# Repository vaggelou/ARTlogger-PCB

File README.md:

# ARTlogger-PCB
This is the PCB design of the ARTlogger, a data logging device for the ART16 racecar.

This is the PCB design for the ARTlogger project, a project that was developed in order to produce a data-logger for racing purpose, during my time in Aristotle Racing Team (ART), the Formula Student team of Aristotle University of Thessaloniki, Greece.

This datalogger was used in the ART16, the 5th race car produced by the team.

The PCB was designed using KiCAD, an open source PCB design tool.

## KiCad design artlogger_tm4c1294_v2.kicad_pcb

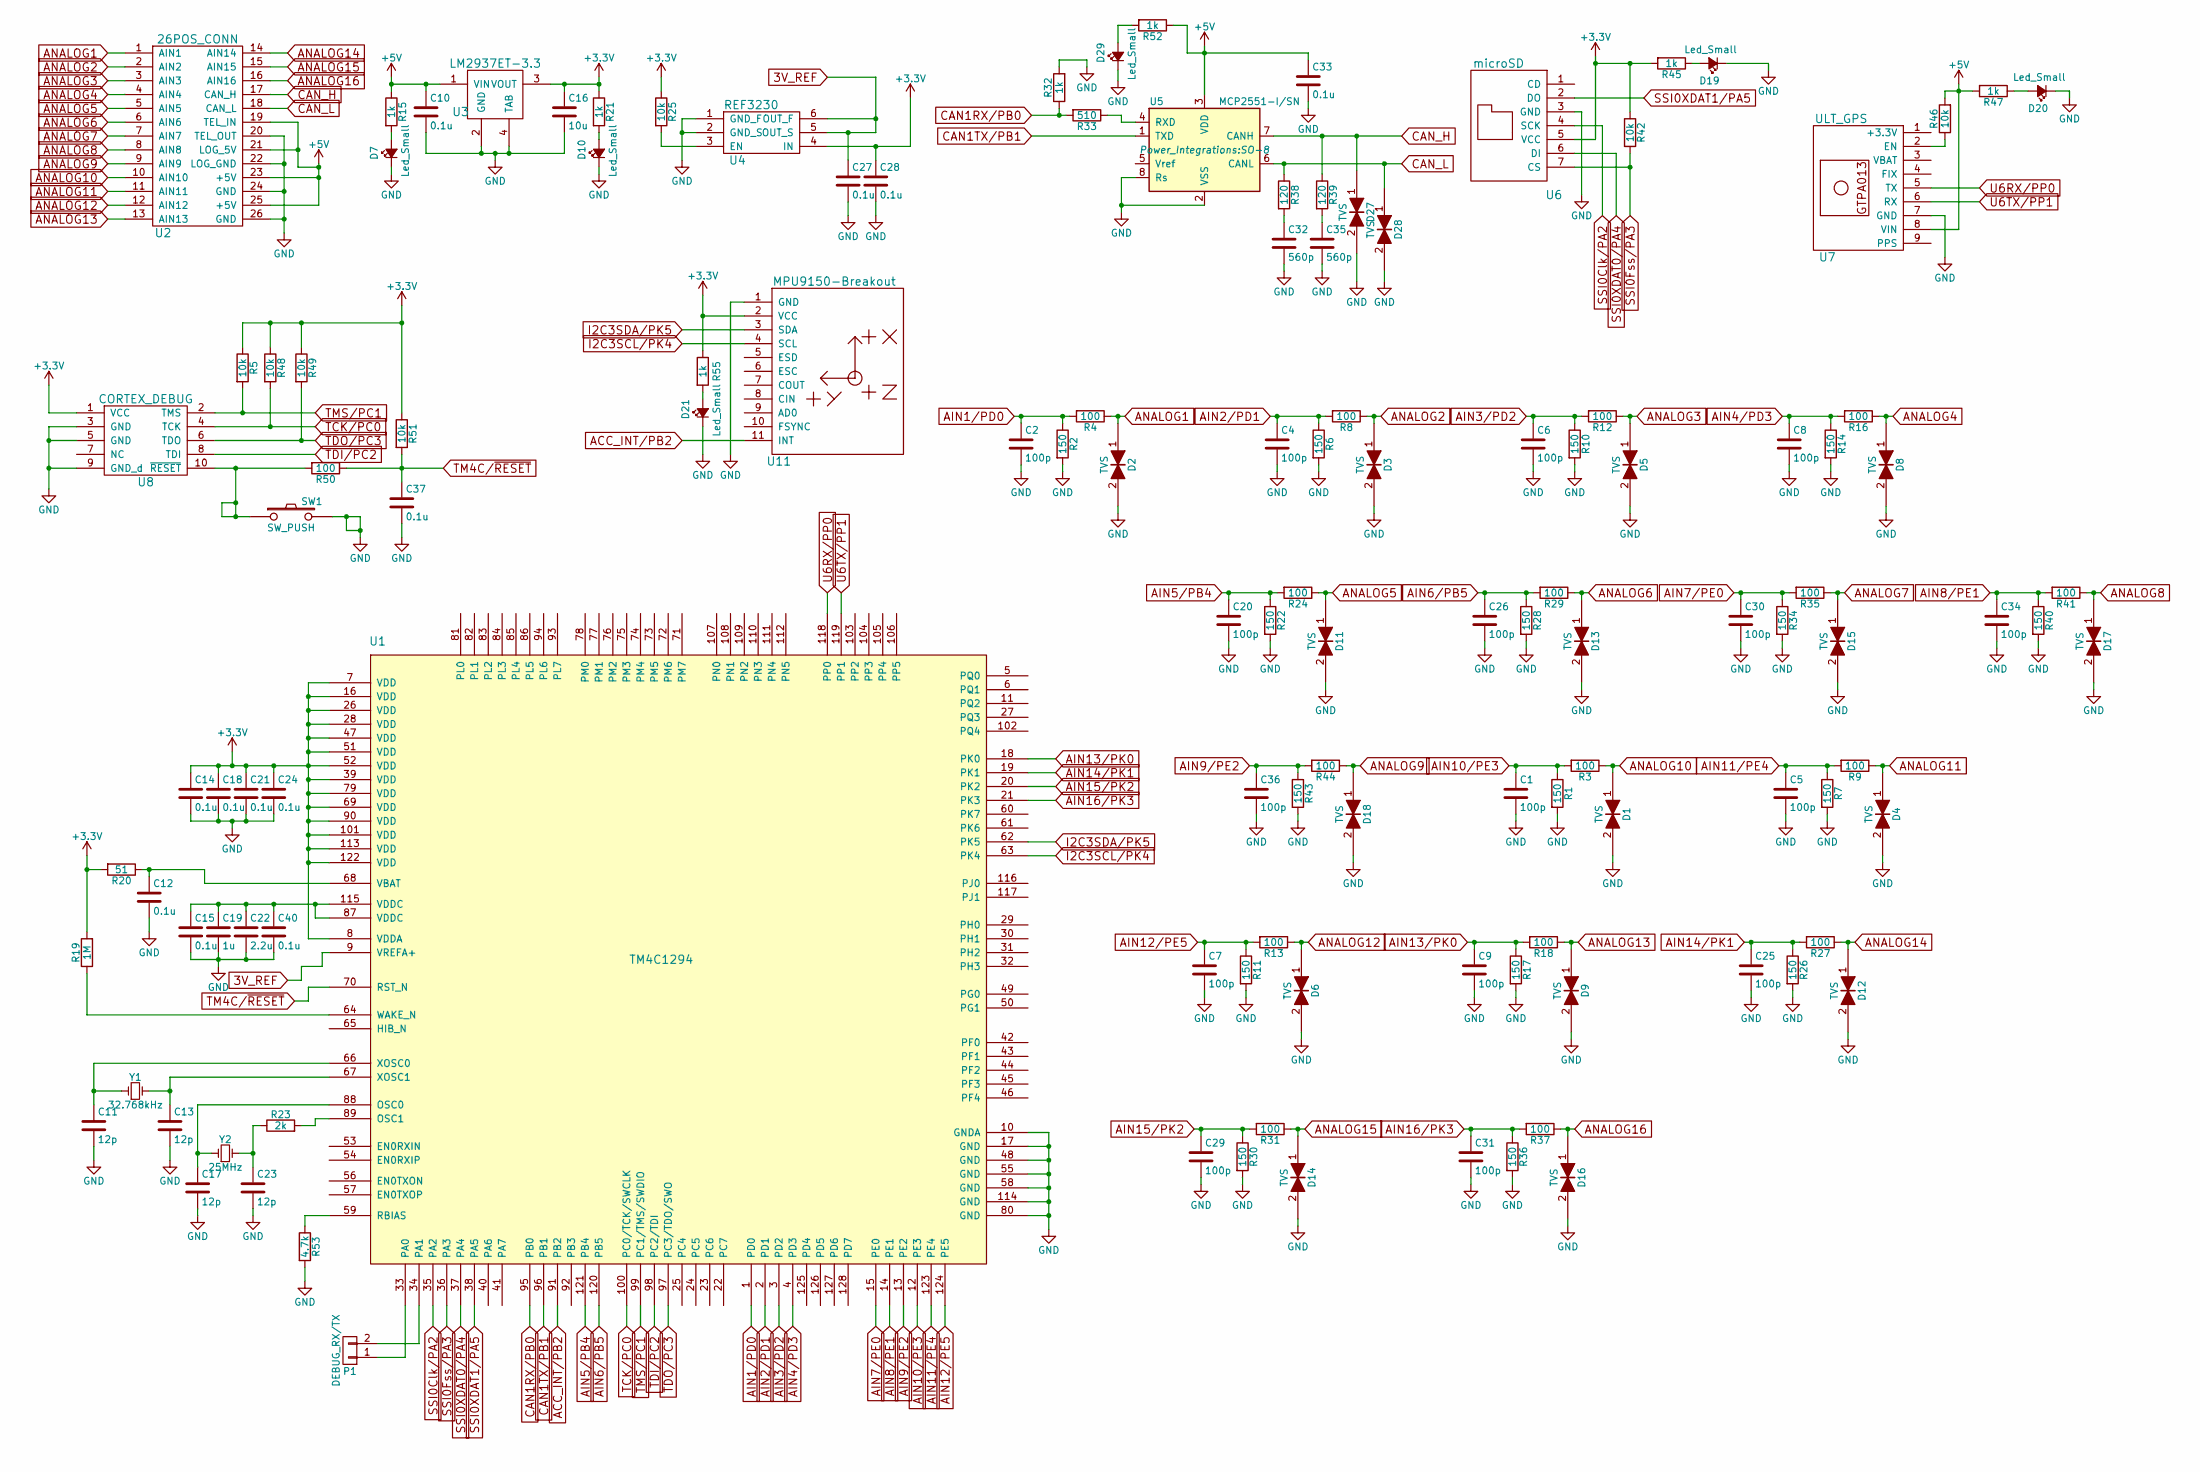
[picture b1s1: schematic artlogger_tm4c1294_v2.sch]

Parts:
C1, C2, C4, C5, C6, C7, C8, C9, C20, C25, C26, C29, C30, C31, C34, C36: 100p; C_0603
C10, C12, C14, C15, C18, C21, C24, C27, C28, C33, C37, C40: 0.1u; C_0603
C11, C13, C17, C23: 12p; C_0603
C16: 10u; C_1206
C19: 1u; C_0805
C22: 2.2u; C_0805
C32, C35: 560p; C_0603
D1, D2, D3, D4, D5, D6, D8, D9, D11, D12, D13, D14, D15, D16, D17, D18, D27, D28: TVS; SOD-523
D7, D10, D19, D20, D21, D29: Led_Small; LED-3MM
P1: DEBUG_RX/TX; Socket_Strip_Straight_1x02
R1, R2, R6, R7, R10, R11, R14, R17, R22, R26, R28, R30, R34, R36, R40, R43: 150; R_0603
R3, R4, R8, R9, R12, R13, R16, R18, R24, R27, R29, R31, R35, R37, R41, R44, R50: 100; R_0603
R5, R25, R42, R46, R48, R49, R51: 10k; R_0603
R15, R21, R32, R45, R47, R52, R55: 1k; R_0603
R19: 1M; R_0603
R20: 51; R_0603
R23: 2k; R_0603
R33: 510; R_0603
R38, R39: 120; R_0603
R53: 4.7k; R_0603
SW1: SW_PUSH; SW_PUSH_SMALL
U1: TM4C1294; TQFP-128_14x14mm_Pitch0.4mm
U2: 26POS_CONN; Socket_Strip_Straight_2x13
U3: LM2937ET-3.3; SOT-223
U4: REF3230; SOT-23-6
U5: MCP2551-I/SN; SO-8
U6: microSD; Socket_Strip_Straight_1x07
U7: ULT_GPS; Socket_Strip_Straight_1x09
U8: CORTEX_DEBUG; IDC_Header_Straight_10pins
U11: MPU9150-Breakout; Socket_Strip_Straight_1x11
Y1: 32.768kHz; CMR200T
Y2: 25MHz; NX5032GA

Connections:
3V_REF: C27.1, U1.9 (VREFA+), U4.5 (OUT_S), U4.6 (OUT_F)
+3V3: C14.1, C16.1, C18.1, C21.1, C24.1, C28.1, R5.1, R19.2, R20.2, R21.1, R25.1, R42.1, R45.2, R48.1, R49.1, R51.1, R55.1, U1.7 (VDD), U1.8 (VDDA), U1.16 (VDD), U1.26 (VDD), U1.28 (VDD), U1.39 (VDD), U1.47 (VDD), U1.51 (VDD), U1.52 (VDD), U1.69 (VDD), U1.79 (VDD), U1.90 (VDD), U1.101 (VDD), U1.113 (VDD), U1.122 (VDD), U3.3 (VOUT), U4.4 (IN), U6.5 (VCC), U8.1 (VCC), U11.2 (VCC)
+5V: C10.1, C33.1, R15.1, R46.2, R47.2, R52.1, U2.19 (TEL_IN), U2.21 (LOG_5V), U2.23 (+5V), U2.25 (+5V), U3.1 (VIN), U5.3 (VDD), U7.8 (VIN)
ACC_INT/PB2: U1.91 (PB2), U11.11 (INT)
AIN1/PD0: C2.1, R2.1, R4.2, U1.1 (PD0)
AIN2/PD1: C4.1, R6.1, R8.2, U1.2 (PD1)
AIN3/PD2: C6.1, R10.1, R12.2, U1.3 (PD2)
AIN4/PD3: C8.1, R14.1, R16.2, U1.4 (PD3)
AIN5/PB4: C20.1, R22.1, R24.2, U1.121 (PB4)
AIN6/PB5: C26.1, R28.1, R29.2, U1.120 (PB5)
AIN7/PE0: C30.1, R34.1, R35.2, U1.15 (PE0)
AIN8/PE1: C34.1, R40.1, R41.2, U1.14 (PE1)
AIN9/PE2: C36.1, R43.1, R44.2, U1.13 (PE2)
AIN10/PE3: C1.1, R1.1, R3.2, U1.12 (PE3)
AIN11/PE4: C5.1, R7.1, R9.2, U1.123 (PE4)
AIN12/PE5: C7.1, R11.1, R13.2, U1.124 (PE5)
AIN13/PK0: C9.1, R17.1, R18.2, U1.18 (PK0)
AIN14/PK1: C25.1, R26.1, R27.2, U1.19 (PK1)
AIN15/PK2: C29.1, R30.1, R31.2, U1.20 (PK2)
AIN16/PK3: C31.1, R36.1, R37.2, U1.21 (PK3)
ANALOG1: D2.1, R4.1, U2.1 (AIN1)
ANALOG2: D3.1, R8.1, U2.2 (AIN2)
ANALOG3: D5.1, R12.1, U2.3 (AIN3)
ANALOG4: D8.1, R16.1, U2.4 (AIN4)
ANALOG5: D11.1, R24.1, U2.5 (AIN5)
ANALOG6: D13.1, R29.1, U2.6 (AIN6)
ANALOG7: D15.1, R35.1, U2.7 (AIN7)
ANALOG8: D17.1, R41.1, U2.8 (AIN8)
ANALOG9: D18.1, R44.1, U2.9 (AIN9)
ANALOG10: D1.1, R3.1, U2.10 (AIN10)
ANALOG11: D4.1, R9.1, U2.11 (AIN11)
ANALOG12: D6.1, R13.1, U2.12 (AIN12)
ANALOG13: D9.1, R18.1, U2.13 (AIN13)
ANALOG14: D12.1, R27.1, U2.14 (AIN14)
ANALOG15: D14.1, R31.1, U2.15 (AIN15)
ANALOG16: D16.1, R37.1, U2.16 (AIN16)
CAN1RX/PB0: R32.1, R33.2, U1.95 (PB0)
CAN1TX/PB1: U1.96 (PB1), U5.1 (TXD)
CAN_H: D27.1, R39.1, U2.17 (CAN_H), U5.7 (CANH)
CAN_L: D28.1, R38.1, U2.18 (CAN_L), U5.6 (CANL)
GND: C1.2, C2.2, C4.2, C5.2, C6.2, C7.2, C8.2, C9.2, C10.2, C11.2, C12.2, C13.2, C14.2, C15.2, C16.2, C17.2, C18.2, C19.2, C20.2, C21.2, C22.2, C23.2, C24.2, C25.2, C26.2, C27.2, C28.2, C29.2, C30.2, C31.2, C32.2, C33.2, C34.2, C35.2, C36.2, C37.2, C40.2, D1.2, D2.2, D3.2, D4.2, D5.2, D6.2, D7.1 (K), D8.2, D9.2, D10.1 (K), D11.2, D12.2, D13.2, D14.2, D15.2, D16.2, D17.2, D18.2, D19.1 (K), D20.1 (K), D21.1 (K), D27.2, D28.2, D29.1 (K), R1.2, R2.2, R6.2, R7.2, R10.2, R11.2, R14.2, R17.2, R22.2, R26.2, R28.2, R30.2, R32.2, R34.2, R36.2, R40.2, R43.2, R53.2, SW1.2, U1.10 (GNDA), U1.17 (GND), U1.48 (GND), U1.55 (GND), U1.58 (GND), U1.80 (GND), U1.114 (GND), U2.20 (TEL_OUT), U2.22 (LOG_GND), U2.24 (GND), U2.26 (GND), U3.2 (GND), U3.4 (TAB), U4.1 (GND_F), U4.2 (GND_S), U5.2 (VSS), U5.8 (Rs), U6.3 (GND), U7.7 (GND), U8.3 (GND), U8.5 (GND), U8.9 (GND_d), U11.1 (GND)
I2C3SCL/PK4: U1.63 (PK4), U11.4 (SCL)
I2C3SDA/PK5: U1.62 (PK5), U11.3 (SDA)
unnamed: C11.1, U1.66 (XOSC0), Y1.1
unnamed: C12.1, R20.1, U1.68 (VBAT)
unnamed: C13.1, U1.67 (XOSC1), Y1.2
unnamed: C15.1, C19.1, C22.1, C40.1, U1.87 (VDDC), U1.115 (VDDC)
unnamed: C17.1, U1.88 (OSC0), Y2.1
unnamed: C23.1, R23.1, Y2.2
unnamed: C32.1, R38.2
unnamed: C35.1, R39.2
unnamed: D7.2 (A), R15.2
unnamed: D10.2 (A), R21.2
unnamed: D19.2 (A), R45.1
unnamed: D20.2 (A), R47.1
unnamed: D21.2 (A), R55.2
unnamed: D29.2 (A), R52.2
unnamed: R19.1, U1.64 (WAKE_N)
unnamed: R23.2, U1.89 (OSC1)
unnamed: R25.2, U4.3 (EN)
unnamed: R33.1, U5.4 (RXD)
unnamed: R46.1, U7.2 (EN)
unnamed: R50.2, SW1.1, U8.10 (~RESET)
unnamed: R53.1, U1.59 (RBIAS)
SSI0Clk/PA2: U1.35 (PA2), U6.4 (SCK)
SSI0Fss/PA3: R42.2, U1.36 (PA3), U6.7 (CS)
SSI0XDAT0/PA4: U1.37 (PA4), U6.6 (DI)
SSI0XDAT1/PA5: U1.38 (PA5), U6.2 (DO)
TCK/PC0: R48.2, U1.100 (PC0/TCK/SWCLK), U8.4 (TCK)
TDI/PC2: U1.98 (PC2/TDI), U8.8 (TDI)
TDO/PC3: R49.2, U1.97 (PC3/TDO/SWO), U8.6 (TDO)
TM4C/~RESET: C37.1, R50.1, R51.2, U1.70 (RST_N)
TMS/PC1: R5.2, U1.99 (PC1/TMS/SWDIO), U8.2 (TMS)
U0RX/PA0: P1.1, U1.33 (PA0)
U0TX/PA1: P1.2, U1.34 (PA1)
U6RX/PP0: U1.118 (PP0), U7.5 (TX)
U6TX/PP1: U1.119 (PP1), U7.6 (RX)

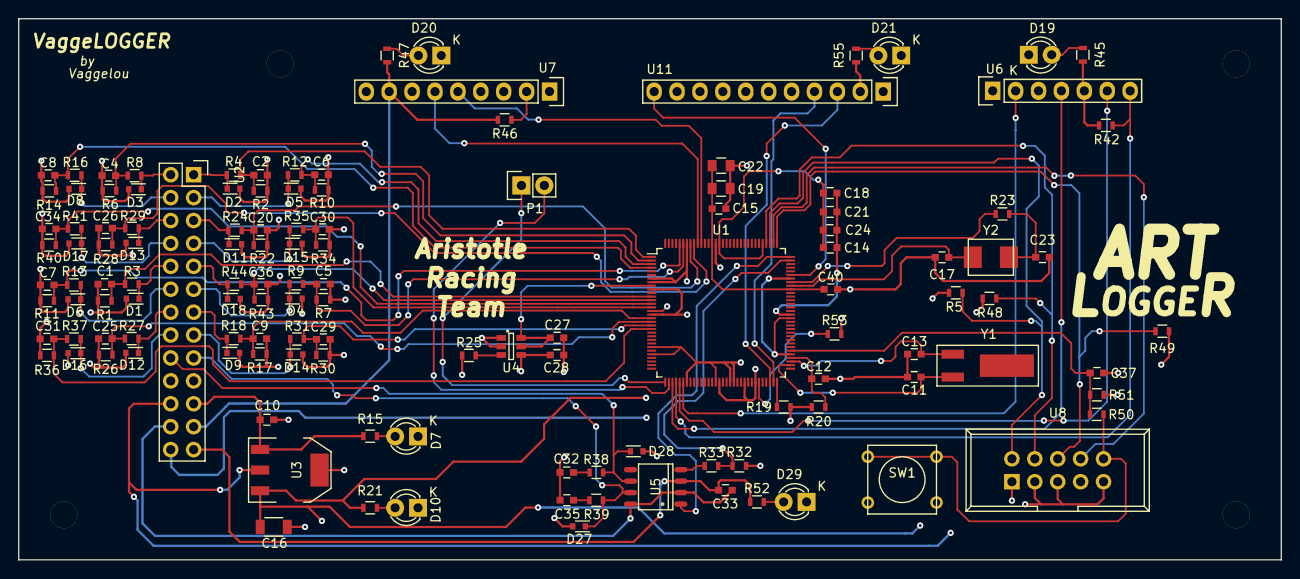
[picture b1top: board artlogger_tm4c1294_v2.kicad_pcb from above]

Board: 4 copper layers, 140.0 x 60.0 mm, 128 parts (0 on the bottom side), 77 nets.
